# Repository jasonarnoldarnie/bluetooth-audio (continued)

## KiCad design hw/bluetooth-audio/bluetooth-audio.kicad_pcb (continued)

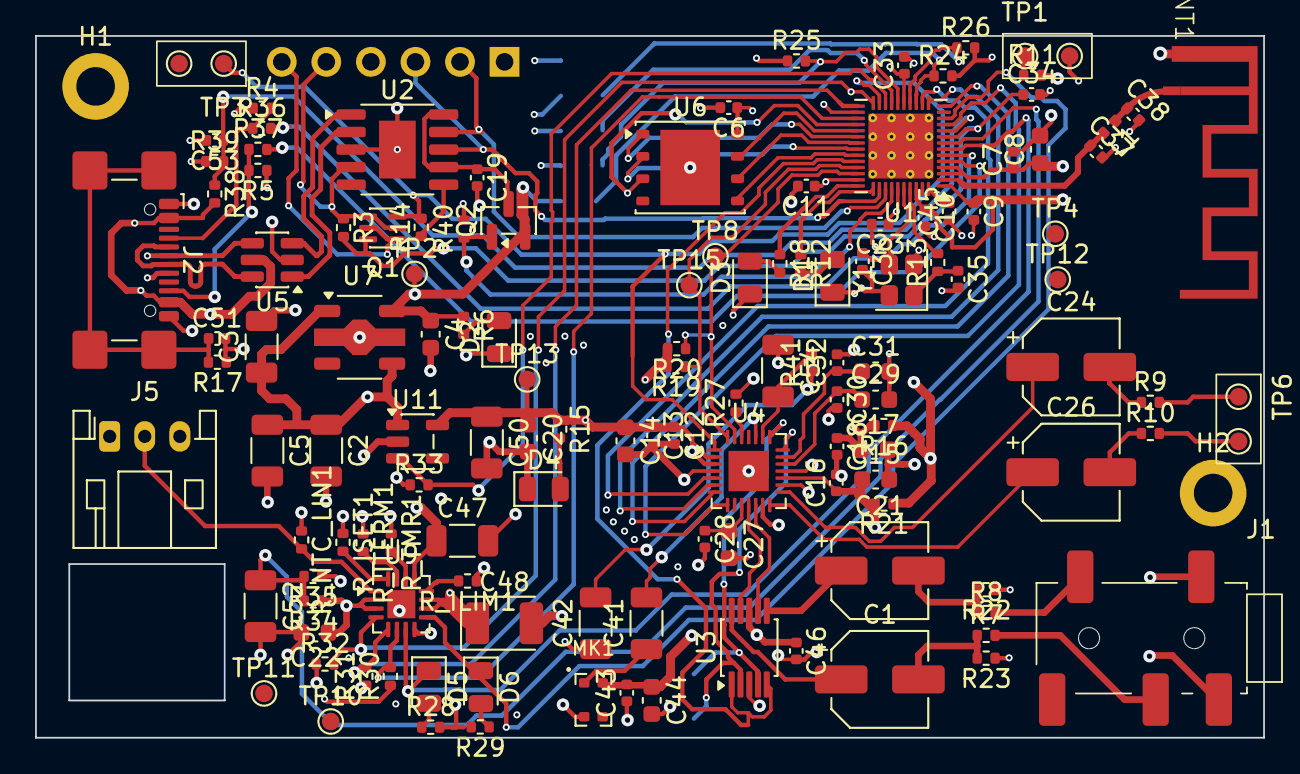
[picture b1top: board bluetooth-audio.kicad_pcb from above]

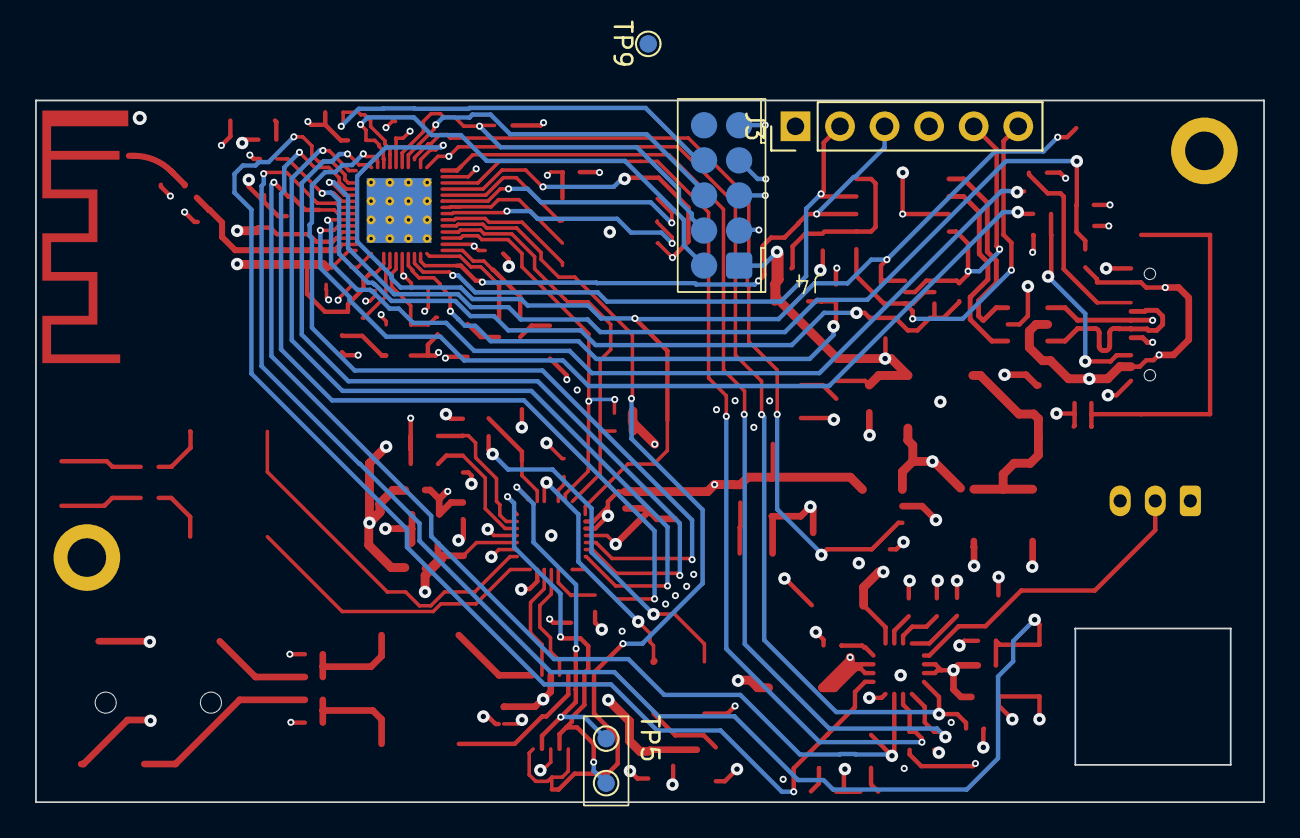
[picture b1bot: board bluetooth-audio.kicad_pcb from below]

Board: 4 copper layers, 70.0 x 40.0 mm, 135 parts (4 on the bottom side), 94 nets.

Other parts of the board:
C23: 100nF; C_0402_1005Metric

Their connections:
+3V3_SYS: C23.1; also elsewhere on the board
GND: C23.2; also elsewhere on the board

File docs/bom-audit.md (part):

# BOM Audit & Cost — bluetooth-audio

**Date:** 2026-09-11 · **Scope:** power, audio, micro sheets · **Sourcing target:** JLCPCB / LCSC

Full footprint + part-number sanity check of the schematic BOM, the corrections applied, the
resulting priced BOM, and the open decisions. Every LCSC code was validated against the local
jlcparts snapshot (CH340K against jlcpcb.com).

## 1. Result summary

- **137 components** audited. Every non-testpoint / non-antenna part carries a consistent
  **Manufacturer + MPN + LCSC** field set. Post-edit verification: no missing LCSC/Manufacturer/MPN,
  no stale `Supplier Part Number` fields.
- Custom parts resolve from the **`kicad-library` git submodule** (`hw/bluetooth-audio/kicad-library`)
  via project-level lib tables using `${KIPRJMOD}` — the project is self-contained on a fresh
  `git clone --recurse-submodules`.
- A **Basic-parts pass** (below) cut JLCPCB Extended parts from 25 → **20** ($75 → $60 one-time).

## 2. Corrections applied

### 2.1 Critical — `C1849` mis-assignment (14 caps)
`C1849` (a 10 µF 16 V 1206 MLCC) had been pasted as a placeholder onto 14 capacitors of
unrelated values (1 µF, 4.7 µF, 47 µF, 4.7 nF, 100 nF, **18 pF crystal load**), several in the
wrong package. All reassigned to the correct part; stale supplier field cleared.

### 2.2 D1 LED
Originally `LED_BLUE` fitted with a **white** LED (`C34499`). Corrected to blue (`C2293`), then —
in the Basic-parts pass — changed to **white (`C34499`, Basic)** since no blue LED is a JLCPCB
Basic part (value relabelled `LED_WHITE`). *The GPIO net is still named `LED_BLUE`; rename in
firmware/schematic if desired. Pick green/yellow instead of white if you prefer — both are Basic.*

### 2.3 Missing passive PNs populated
All resistors, caps and L1 given JLCPCB parts — Basic where available. Dielectric chosen
deliberately: **C0G** for the 18 pF crystal-load caps (C35/C36) and the 3.3 pF RF-match caps
(C37/C38); **C0G preserved** on the audio 100 nF (C41/C42, `C97946`); X7R/X5R for decoupling.

### 2.4 Part / footprint changes
| Ref | Change | Part |
|-----|--------|------|
| C48 | 47 µF SYS bulk: MLCC → **tantalum** (footprint `CP_EIA-3528-21_Kemet-B`) | `C22036` Kyocera AVX |
| C27 | 10 µF footprint **0402 → 0603** | `C19702` |
| C51 | USB-shield 4.7 nF: **1206 → 0402**, now **Basic** (generic filter) | `C1538` |
| R_TMR1 / R_ISET1 / R_ITERM1 | charger 56 k / 1.2 k / 3 k: **0402 → 0603** to get **Basic** at the *same values* (charger programming unchanged) | `C23206` / `C22765` / `C4211` |
| U3  | footprint **TSSOP-10 → MSOP-10** (DGS = VSSOP, no pad) | `C42751` |
| Q2  | PN added | `C15127` (Basic) |
| J2  | PN added | `C5143397` GCT USB4110-GF-A |
| J5  | Molex → **JST-PH 3-pin** battery connector | `C157929` JST S3B-PH-K-S |
| D6  | LED_CHG → **amber** | `C2296` |
| U9  | **DNP** (charger not populated) | `C54313` (kept for reference) |

### 2.5 Field normalisation
All ICs/LEDs/discretes migrated from `Supplier Part Number` to `LCSC` + `Manufacturer` + `MPN`
(incl. secondary units of multi-unit symbols D7/D8/Q1).

## 3. MLCC review (power rail)

Roles from the PCB netlist: C47 = VBUS input; C2/C3/C5 = SYS & LDO inputs; **C48 = +V_SYS bulk,
C49 = +BATT bulk**; C4/C20/C50 = 3V3 rails; C51 = USB-shield Y-cap; C52/C53 = ADC / VBUS-sense.

- **Decoupling + all three regulators → MLCC is correct** (low-ESR ceramic by design). Using 1206
  for the rail caps already limits DC-bias loss (50 V parts selected).
- **C48 (SYS bulk) → 47 µF/10 V tantalum** (`C22036`): a 10 V X5R 47 µF 1206 on a 3.0–4.4 V rail
  gives only ~50–65 % of nameplate under bias; the tantalum holds value.
- **C49 (+BATT bulk) left as MLCC** — revisit if battery-node hold-up matters.

## 4. Priced BOM (assembled parts; DNP excluded)

Unit price at the 100-board tier. Lib = JLCPCB Basic (free feeder) vs Extended ($3 one-time each).

| Qty | Value | Refs | Footprint | Manufacturer | MPN | LCSC | Lib | Unit(100) |
|----:|-------|------|-----------|--------------|-----|------|-----|----------:|
| 14 | 100nF | C9,C10,C11,C12,C13,C16,C18,C19,C28,C30,C32,C33,C43,C46 | C_0402_1005Metric | Samsung Electro Mechanics | CL05B104KO5NNNC | C1525 | Basic | $0.0051 |
| 10 | 100k | R17,R22,R23,R30,R31,R34,R35,R38,R39,R40 | R_0402_1005Metric | UNI ROYAL Uniroyal Elec | 0402WGF1003TCE | C25741 | Basic | $0.0033 |
| 8 | 10u | C8,C14,C15,C17,C27,C29,C31,C44 | C_0603_1608Metric | Samsung Electro Mechanics | CL10A106KP8NNNC | C19702 | Basic | $0.0723 |
| 6 | 1k | R19,R20,R32,R33,R36,R37 | R_0402_1005Metric | UNI ROYAL Uniroyal Elec | 0402WGF1001TCE | C11702 | Basic | $0.0011 |
| 6 | 10R | R7,R8,R9,R10,R16,R21 | R_0402_1005Metric | UNI ROYAL Uniroyal Elec | 0402WGF100JTCE | C25077 | Basic | $0.0009 |
| 6 | 330R | R6,R12,R15,R18,R28,R29 | R_0402_1005Metric | UNI ROYAL Uniroyal Elec | 0402WGF3300TCE | C25104 | Basic | $0.0012 |
| 5 | 1uF | C6,C7,C24,C26,C34 | C_0402_1005Metric | Samsung Electro Mechanics | CL05A105KA5NQNC | C52923 | Basic | $0.0122 |
| 4 | LED_PGOOD | D2,D3,D4,D5 | LED_0805_2012Metric | Hubei KENTO Elec | KT-0805G | C2297 | Basic | $0.0163 |
| 4 | 10k | R1,R2,R11,R27 | R_0402_1005Metric | UNI ROYAL Uniroyal Elec | 0402WGF1002TCE | C25744 | Basic | $0.0029 |
| 3 | 10uF | C5,C47,C50 | C_1206_3216Metric | Samsung Electro Mechanics | CL31A106KBHNNNE | C13585 | Basic | $0.1622 |
| 2 | 18pF | C35,C36 | C_0402_1005Metric | FH Guangdong Fenghua Advanced Tech | 0402CG180J500NT | C1549 | Basic | $0.0023 |
| 2 | 4.7uF | C4,C22 | C_0603_1608Metric | Samsung Electro Mechanics | CL10A475KO8NNNC | C19666 | Basic | $0.0209 |
| 2 | 100nF | C52,C53 | C_1206_3216Metric | Samsung Electro Mechanics | CL31B104KBCNNNC | C24497 | Basic | $0.0188 |
| 2 | 4k7 | R24,R25 | R_0402_1005Metric | UNI ROYAL Uniroyal Elec | 0402WGF4701TCE | C25900 | Basic | $0.0011 |
| 2 | 5k1 | R4,R5 | R_0402_1005Metric | UNI ROYAL Uniroyal Elec | 0402WGF5101TCE | C25905 | Basic | $0.0009 |
| 2 | 47uF | C1,C21 | CP_Elec_5x5.8 | PANASONIC | EEEFT1E470AR | C336270 | Ext | $0.3106 |
| 2 | D_Schottky_Dual_Series_AKC_Split | D7,D8 | SOT-23 | MDD Microdiode Semiconductor | BAT54S | C408389 | Ext | $0.0137 |
| 2 | 3.3pF | C37,C38 | C_0402_1005Metric | Murata Electronics | GJM1555C1H3R3BB01D | C76906 | Ext | $0.0318 |
| 2 | 100nF | C41,C42 | C_1206_3216Metric_Pad1.33x1.80mm_HandSolder | Murata Electronics | GRM31C5C1H104JA01L | C97946 | Ext | $0.1513 |
| 1 | AO3401A | Q2 | SOT-23 | Alpha Omega Semicon | AO3401A | C15127 | Basic | $0.0596 |
| 1 | 10nF | C45 | C_0402_1005Metric | Samsung Electro Mechanics | CL05B103KB5NNNC | C15195 | Basic | $0.0035 |
| 1 | 4.7nF | C51 | C_0402_1005Metric | FH Guangdong Fenghua Advanced Tech | 0402B472K500NT | C1538 | Basic | $0.0042 |
| 1 | Conn_01x03 | J5 | JST_PH_S3B-PH-K_1x03_P2.00mm_Horizontal | JST | S3B-PH-K-S(LF)(SN) | C157929 | Ext | $0.0402 |
| 1 | 1uF | C20 | C_0603_1608Metric | Samsung Electro Mechanics | CL10A105KB8NNNC | C15849 | Basic | $0.0297 |
| 1 | 0R | R13 | R_0402_1005Metric | UNI ROYAL Uniroyal Elec | 0402WGF0000TCE | C17168 | Basic | $0.0011 |
| 1 | 1uF | C2 | C_1206_3216Metric | Samsung Electro Mechanics | CL31B105KBHNNNE | C1848 | Basic | $0.0414 |
| 1 | 47uF | C48 | CP_EIA-3528-21_Kemet-B | Kyocera AVX | TAJB476K010RNJ | C22036 | Ext | $0.1847 |
| 1 | 1k2 | R_ISET1 | R_0603_1608Metric | UNI ROYAL Uniroyal Elec | 0603WAF1201T5E | C22765 | Basic | $0.0015 |
| 1 | LED_CHG | D6 | LED_0805_2012Metric | Hubei KENTO Elec | KT-0805Y | C2296 | Basic | $0.0153 |
| 1 | 56k | R_TMR1 | R_0603_1608Metric | UNI ROYAL Uniroyal Elec | 0603WAF5602T5E | C23206 | Basic | $0.0020 |
| 1 | Crystal 40 MHz 10pF | Y1 | Crystal_SMD_SeikoEpson_FA128-4Pin_2.0x1.6mm | Seiko Epson | Q22FA12800101 | C255898 | Ext | $0.2268 |
| 1 | 1k5 | R_ILIM1 | R_0402_1005Metric | UNI ROYAL Uniroyal Elec | 0402WGF1501TCE | C25867 | Basic | $0.0011 |
| 1 | PJ-3537S-SMT | J1 | PJ-3537S-SMT | XKB Connection | PJ-3537S-SMT | C2689709 | Ext | $0.2473 |
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
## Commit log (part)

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2024-10-28 Adding blank Kicad project
2024-10-30 Created power schematic with buck converter and LDO. Including calculations and datasheets
2024-10-31 Microcontroller schematic sheet with decoupling, crystals, RF matching etc. Various app notes
2025-04-05 Adding app notes and datasheets
2025-04-05 Custom footprints for microphone, jtag header, antenna and dual testpoint
2025-04-05 Updated design doc
2025-04-05 Completed design with ESP32D0WD-v3, and JLC production files. High production cost due to req of PCBA standard, due to ESP32 pin pitch.
2025-04-15 Custom symbol and footprints for IS2083. Updated design document. Initial dump of components onto cleared PCB.
2025-04-16 All decoupling caps and labels on IS2083
2025-04-19 Fixing sheet titles
2025-08-02 Production files initial creation
2025-08-02 TODO diff
